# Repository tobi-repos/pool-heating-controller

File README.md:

# pool-heating-controller
Control heating pump of a pool depending on external conditions.

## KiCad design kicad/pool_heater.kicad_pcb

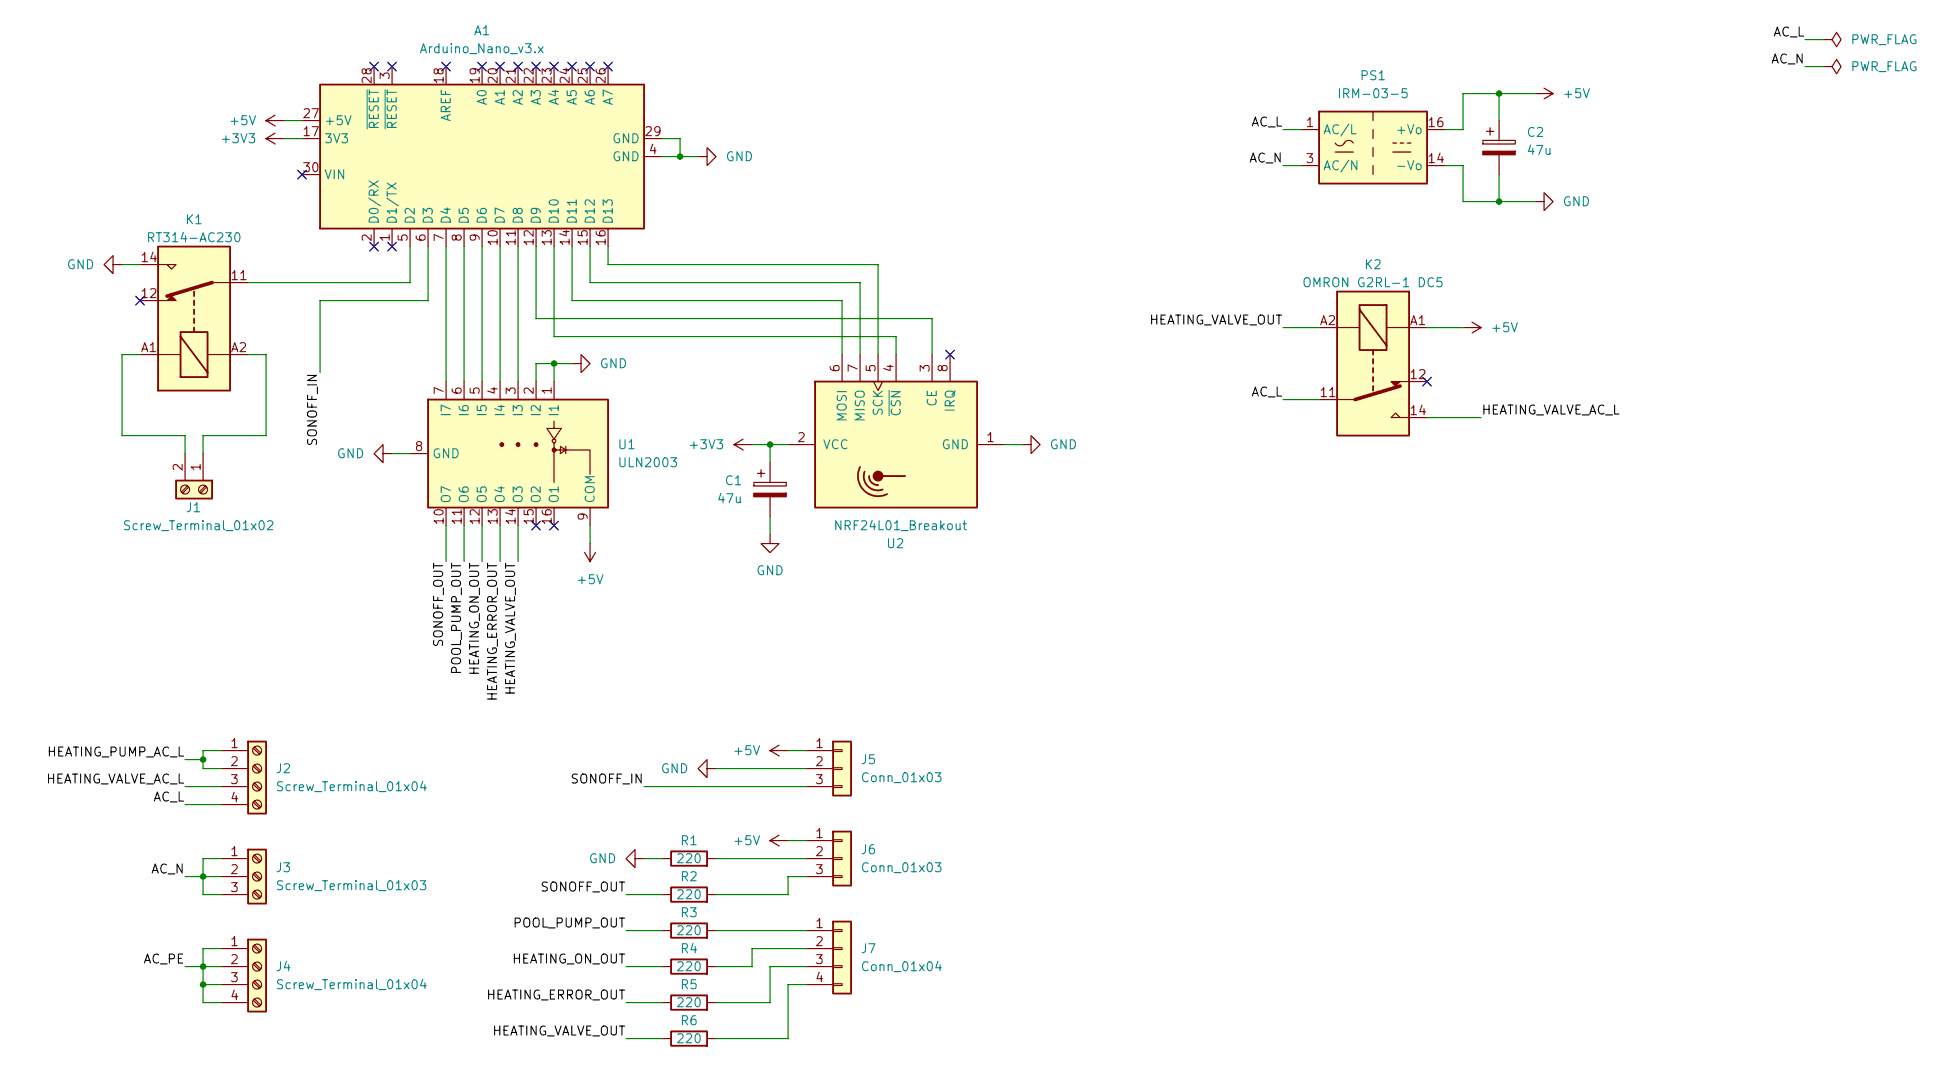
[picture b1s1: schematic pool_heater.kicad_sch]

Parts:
A1: Arduino_Nano_v3.x; Arduino_Nano
C1, C2: 47u; CP_Radial_D8.0mm_P3.50mm
J1: Screw_Terminal_01x02; TerminalBlock_bornier-2_P5.08mm
J2, J4: Screw_Terminal_01x04; TerminalBlock_bornier-4_P5.08mm
J3: Screw_Terminal_01x03; TerminalBlock_bornier-3_P5.08mm
J5, J6: Conn_01x03; JST_XH_B3B-XH-A_1x03_P2.50mm_Vertical
J7: Conn_01x04; JST_XH_B4B-XH-A_1x04_P2.50mm_Vertical
K1: RT314-AC230; Relay_SPDT_Schrack-RT1-16A-FormC_RM5mm
K2: OMRON G2RL-1 DC5; Relay_SPDT_Finder_40.31
PS1: IRM-03-5; Converter_ACDC_MeanWell_IRM-03-xx_THT
R1, R2, R3, R4, R5, R6: 220; R_1206_3216Metric_Pad1.30x1.75mm_HandSolder
U1: ULN2003; DIP-16_W7.62mm_Socket_LongPads
U2: NRF24L01_Breakout; NRF24

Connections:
+3V3: A1.17 (3V3), C1.1, U2.2 (VCC)
+5V: A1.27 (+5V), C2.1, J5.1, J6.1, K2.A1, PS1.16 (+Vo), U1.9 (COM)
/AC_L: J2.4, K2.11, PS1.1 (AC/L)
/AC_N: J3.1, J3.2, J3.3, PS1.3 (AC/N)
/AC_PE: J4.1, J4.2, J4.3, J4.4
/HEATING_ERROR_OUT: R5.1, U1.13 (O4)
/HEATING_ON_OUT: R4.1, U1.12 (O5)
/HEATING_PUMP_AC_L: J2.1, J2.2
/HEATING_VALVE_AC_L: J2.3, K2.14
/HEATING_VALVE_OUT: K2.A2, R6.1, U1.14 (O3)
/POOL_PUMP_OUT: R3.1, U1.11 (O6)
/SONOFF_IN: A1.6 (D3), J5.3
/SONOFF_OUT: R2.1, U1.10 (O7)
GND: A1.4 (GND), A1.29 (GND), C1.2, C2.2, J5.2, K1.14, PS1.14 (-Vo), R1.1, U1.1 (I1), U1.2 (I2), U1.8 (GND), U2.1 (GND)
unnamed: A1.5 (D2), K1.11
unnamed: A1.7 (D4), U1.7 (I7)
unnamed: A1.8 (D5), U1.6 (I6)
unnamed: A1.9 (D6), U1.5 (I5)
unnamed: A1.10 (D7), U1.4 (I4)
unnamed: A1.11 (D8), U1.3 (I3)
unnamed: A1.12 (D9), U2.3 (CE)
unnamed: A1.13 (D10), U2.4 (~CSN)
unnamed: A1.14 (D11), U2.6 (MOSI)
unnamed: A1.15 (D12), U2.7 (MISO)
unnamed: A1.16 (D13), U2.5 (SCK)
unnamed: J1.1, K1.A2
unnamed: J1.2, K1.A1
unnamed: J6.2, R1.2
unnamed: J6.3, R2.2
unnamed: J7.1, R3.2
unnamed: J7.2, R4.2
unnamed: J7.3, R5.2
unnamed: J7.4, R6.2

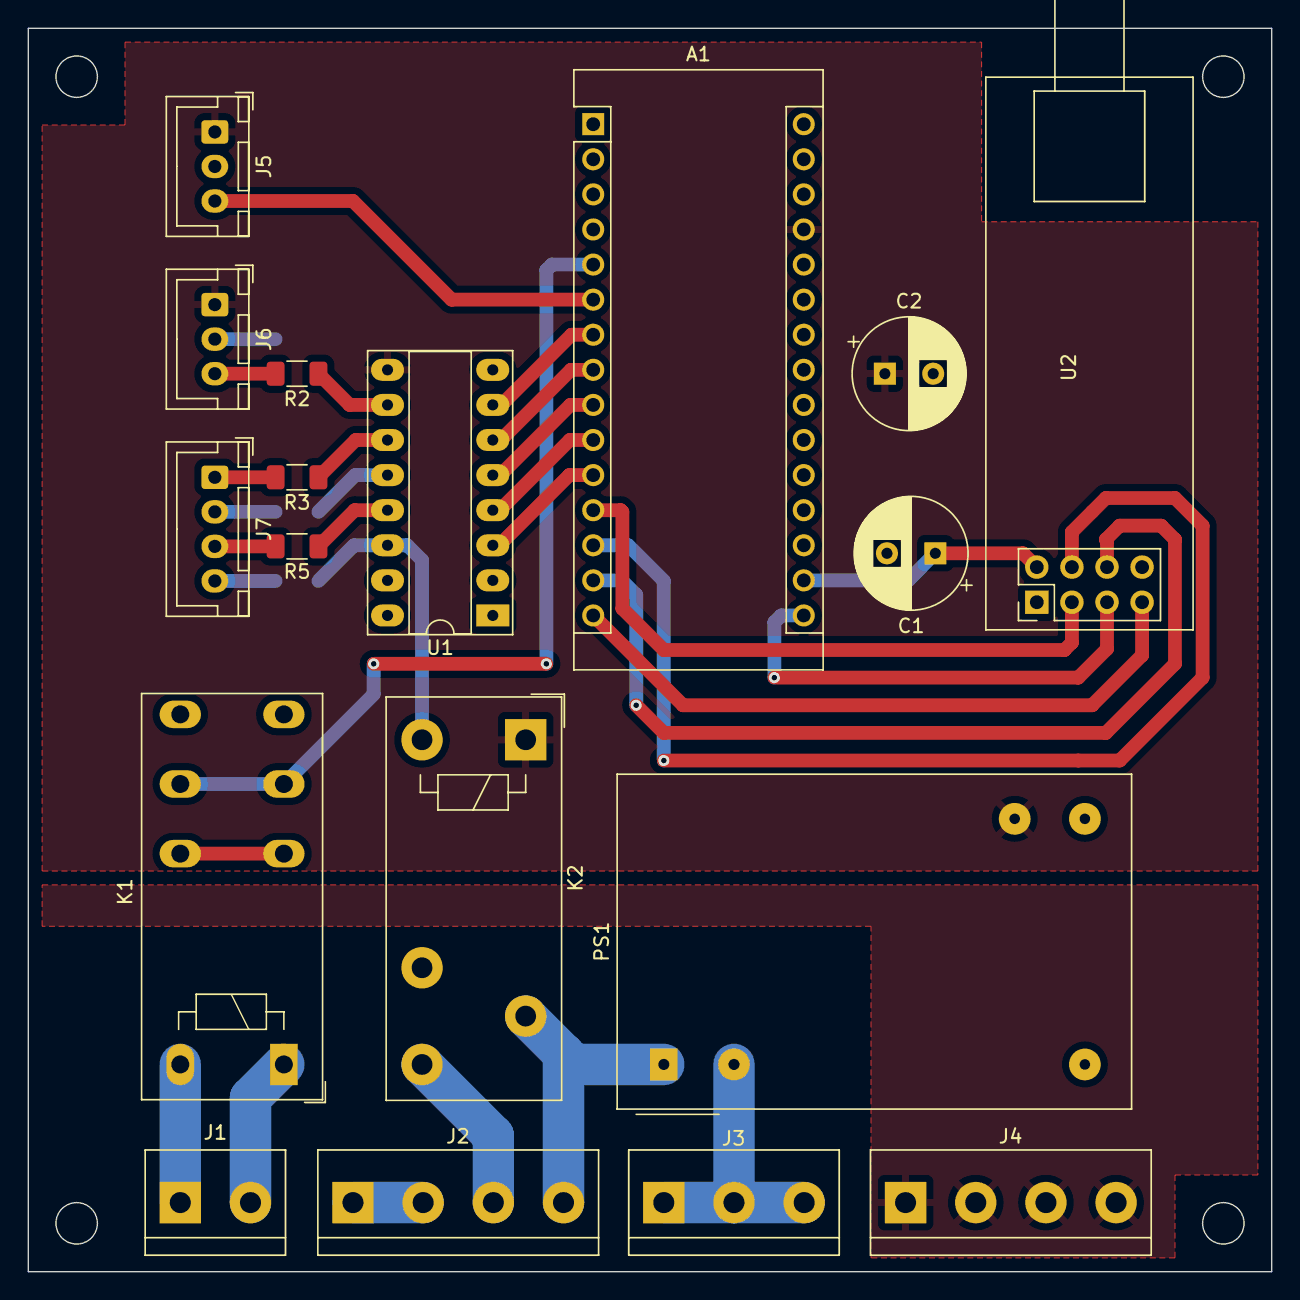
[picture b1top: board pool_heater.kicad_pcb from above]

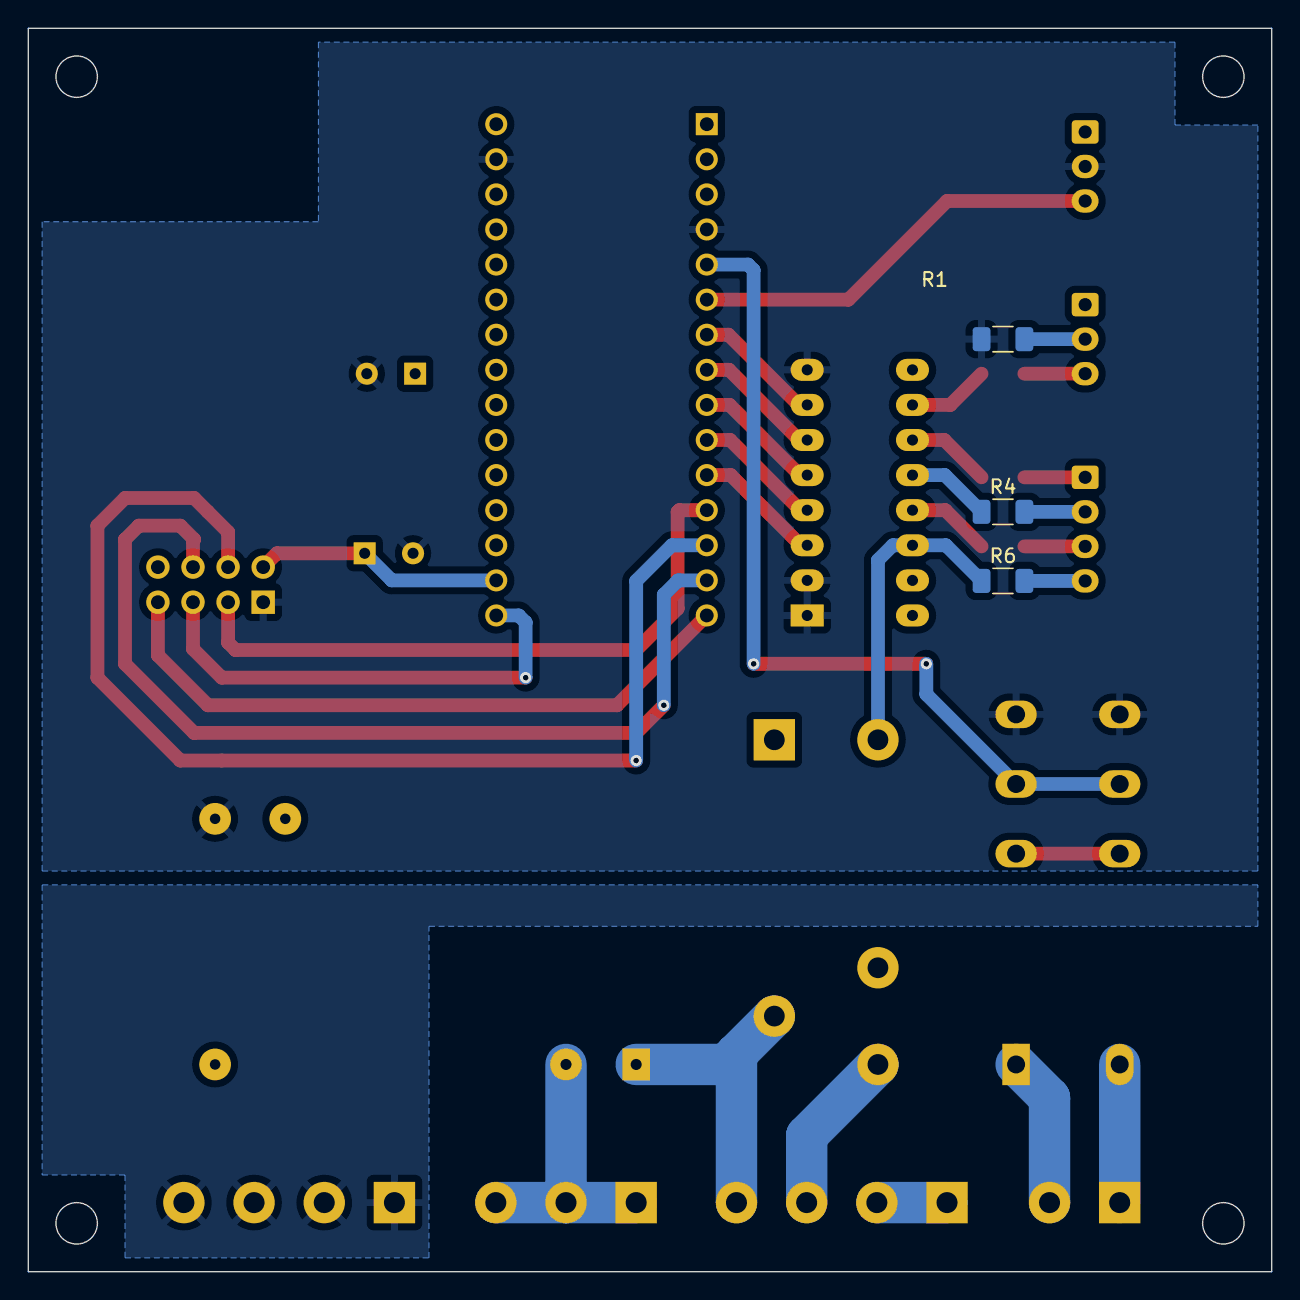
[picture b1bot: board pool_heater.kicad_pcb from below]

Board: 2 copper layers, 90.0 x 90.0 mm, 21 parts (3 on the bottom side), 33 nets.

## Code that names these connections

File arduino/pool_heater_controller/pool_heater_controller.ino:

#include <RF24.h>

#define WITH_RADIO 0

static const int POOL_PUMP_IN = 2;
static const int SONOFF_IN = 3;
static const int SONOFF_OUT = 4;
static const int POOL_PUMP_OUT = 5;
static const int HEATING_SYS_OUT = 6;
static const int HEATING_SYS_ERR_OUT = 7;
static const int HEATING_VALVE_OUT = 8;

#if WITH_RADIO
static const int RF_CE = 9;
static const int RF_CSN = 10;

static RF24 radio(RF_CE, RF_CSN);

static const uint8_t radioId[5] = "POOL";
static uint8_t radioPayload[1] = {0};
static uint32_t lastRadioMessage = 0;
#endif

static bool poolPumpOk = false;
static bool sonoffOk = false;
static bool heatingSysOk = false;
static bool conditionsFulfilled = false;
static uint32_t conditionsFulfilledTime = 0;

void setup()
{
	pinMode(POOL_PUMP_IN, INPUT_PULLUP);
	pinMode(SONOFF_IN, INPUT_PULLUP);
	pinMode(SONOFF_OUT, OUTPUT);
	pinMode(POOL_PUMP_OUT, OUTPUT);
	pinMode(HEATING_SYS_OUT, OUTPUT);
	pinMode(HEATING_SYS_ERR_OUT, OUTPUT);
	pinMode(HEATING_VALVE_OUT, OUTPUT);

#if WITH_RADIO
	radio.begin();
	radio.setChannel(1);
	radio.setPALevel(RF24_PA_LOW);
	radio.setAddressWidth(4);
	radio.setPayloadSize(sizeof(radioPayload));
	radio.openReadingPipe(0, radioId);
	radio.startListening();
#else
    heatingSysOk = true;
#endif
}

void loop()
{
	uint32_t t = millis();

	if (!digitalRead(POOL_PUMP_IN))
	{
		digitalWrite(POOL_PUMP_OUT, HIGH);
		poolPumpOk = true;
	}
	else
	{
		digitalWrite(POOL_PUMP_OUT, LOW);
		poolPumpOk = false;
	}
	
	if (digitalRead(SONOFF_IN))
	{
		digitalWrite(SONOFF_OUT, HIGH);
		sonoffOk = true;
	}
	else
	{
		digitalWrite(SONOFF_OUT, LOW);
		sonoffOk = false;
	}
	
#if WITH_RADIO
	if (radio.available())
	{
		radio.read(radioPayload, sizeof(radioPayload));
		lastRadioMessage = t;

		digitalWrite(HEATING_SYS_ERR_OUT, LOW);

		if (*radioPayload)
		{
			digitalWrite(HEATING_SYS_OUT, HIGH);
			heatingSysOk = true;
		}
		else
		{
			digitalWrite(HEATING_SYS_OUT, LOW);
			heatingSysOk = false;
		}
	}
	else if(t - lastRadioMessage > 30000)
	{
		digitalWrite(HEATING_SYS_OUT, LOW);
		digitalWrite(HEATING_SYS_ERR_OUT, HIGH);
		heatingSysOk = false;
	}
#else
    digitalWrite(HEATING_SYS_ERR_OUT, LOW);
    digitalWrite(HEATING_SYS_OUT, HIGH);
#endif

	if (conditionsFulfilled)
	{
		if (poolPumpOk && sonoffOk && heatingSysOk)
		{
			if (t - conditionsFulfilledTime > 2000)
				digitalWrite(HEATING_VALVE_OUT, HIGH);
			else
				digitalWrite(HEATING_VALVE_OUT, LOW);
		}
		else
		{
			digitalWrite(HEATING_VALVE_OUT, LOW);
			conditionsFulfilled = false;
		}
	}
	else if (poolPumpOk && sonoffOk && heatingSysOk)
	{
		conditionsFulfilled = true;
		conditionsFulfilledTime = t;
	}
}

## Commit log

2023-08-17 Added all project files.
2024-05-14 Added installation instructions.
2024-05-14 Added flag to disable radio module.
